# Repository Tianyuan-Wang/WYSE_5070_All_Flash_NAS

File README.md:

# WYSE_5070_All_Flash_NAS

最近买了个二手的WYSE 5070瘦客户机打算用作低功耗NAS。由于不是Extended版本，需要对硬件进行改动来安装额外的硬盘。

之前看了[KCORES的教程](https://youtu.be/9opQ4gsh4Hg?si=m19QCSclOVte6yVY)，给主板加了PCIE插槽但是配套的Riser卡放不进机箱，而且需要搭配12V电源。

于是一切为了美观，设计了一个自带19V转12V的矮版转接卡，配合PCIE桥接卡可以拓展4个M.2 NVME SSD。配合机箱内部预留的螺丝孔位，正好可以3D打印个支架用来固定扩展卡。

## 硬件改动

1. 需要切掉原本用来固定背板扩展卡的两个金属片。以及将3D打印的NVME扩展卡支架用M3x10螺丝安装到机箱内。

2. 需要将NVME扩展卡末端切掉5mm，否则机箱盖子盖不上。（这里用的是SSU SU-EM5204(A3)版的扩展卡，链接就不放了，某宝有卖。）没用更高速的版本是因为散热器高度的问题，这里我把原本10mm的散热片剪成了6mm高度，正好能放下。如果能找到合适的散热片，推荐买高速版本，因为5204-A3上行是3.0x2而主板是2.0x4，浪费了很多。机箱外壳是金属的，可以加散热贴通过机箱散热。

## 安装注意

1. 安装扩展卡的时候，要先把NVME扩展卡插入Riser卡里再一起插入主板PCIE插槽，否则没法装扩展卡。

2. 如果是和我一样用的无EMMC版本的，需要先安装扩展卡支架再安装主板上的SATA SSD。

## 示意图

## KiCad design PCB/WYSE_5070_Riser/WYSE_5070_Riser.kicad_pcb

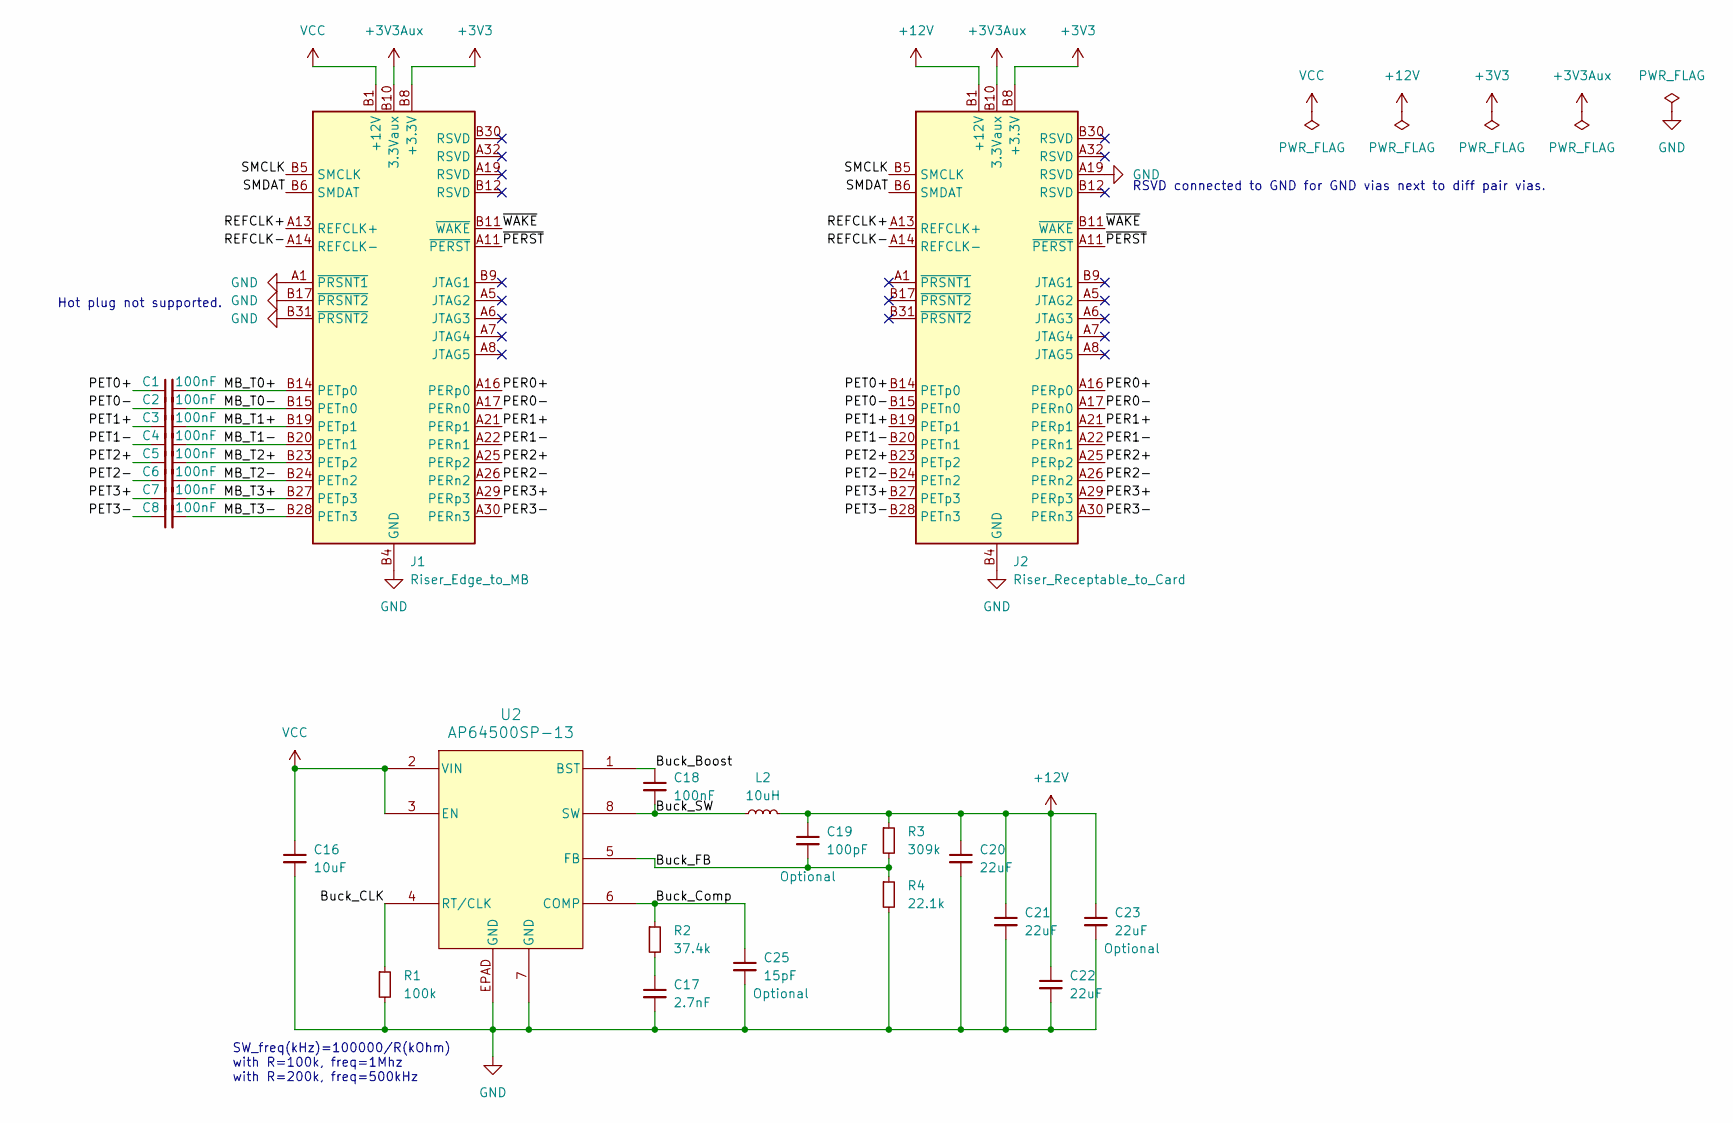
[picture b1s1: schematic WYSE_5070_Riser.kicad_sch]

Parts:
C1, C2, C3, C4, C5, C6, C7, C8, C18: 100nF; C_0402_1005Metric
C16: 10uF; C_1206_3216Metric
C17: 2.7nF; C_0402_1005Metric
C19: 100pF; C_0402_1005Metric
C20, C21, C22, C23: 22uF; C_0805_2012Metric
C25: 15pF; C_0402_1005Metric
J1: Riser_Edge_to_MB; BUS_PCIexpress_x4_Short
J2: Riser_Receptable_to_Card; PCIEx4_SMD_Narrow
L2: 10uH; L_Bourns_SRP1038C_10.0x10.0mm
R1: 100k; R_0402_1005Metric
R2: 37.4k; R_0402_1005Metric
R3: 309k; R_0402_1005Metric
R4: 22.1k; R_0402_1005Metric
U2: AP64500SP-13; SO-8EP_DIO

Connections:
+3V3: J1.A9 (+3.3V), J1.A10 (+3.3V), J1.B8 (+3.3V), J2.A9 (+3.3V), J2.A10 (+3.3V), J2.B8 (+3.3V)
+3V3Aux: J1.B10 (3.3Vaux), J2.B10 (3.3Vaux)
+12V: C19.1, C20.1, C21.1, C22.1, C23.1, J2.A2 (+12V), J2.A3 (+12V), J2.B1 (+12V), J2.B2 (+12V), J2.B3 (+12V), L2.2, R3.1
/Buck_Boost: C18.1, U2.1 (BST)
/Buck_CLK: R1.1, U2.4 (RT/CLK)
/Buck_Comp: C25.1, R2.1, U2.6 (COMP)
/Buck_FB: C19.2, R3.2, R4.1, U2.5 (FB)
/Buck_SW: C18.2, L2.1, U2.8 (SW)
/MB_T0+: C1.2, J1.B14 (PETp0)
/MB_T0-: C2.2, J1.B15 (PETn0)
/MB_T1+: C3.2, J1.B19 (PETp1)
/MB_T1-: C4.2, J1.B20 (PETn1)
/MB_T2+: C5.2, J1.B23 (PETp2)
/MB_T2-: C6.2, J1.B24 (PETn2)
/MB_T3+: C7.2, J1.B27 (PETp3)
/MB_T3-: C8.2, J1.B28 (PETn3)
/PER0+: J1.A16 (PERp0), J2.A16 (PERp0)
/PER0-: J1.A17 (PERn0), J2.A17 (PERn0)
/PER1+: J1.A21 (PERp1), J2.A21 (PERp1)
/PER1-: J1.A22 (PERn1), J2.A22 (PERn1)
/PER2+: J1.A25 (PERp2), J2.A25 (PERp2)
/PER2-: J1.A26 (PERn2), J2.A26 (PERn2)
/PER3+: J1.A29 (PERp3), J2.A29 (PERp3)
/PER3-: J1.A30 (PERn3), J2.A30 (PERn3)
/PET0+: C1.1, J2.B14 (PETp0)
/PET0-: C2.1, J2.B15 (PETn0)
/PET1+: C3.1, J2.B19 (PETp1)
/PET1-: C4.1, J2.B20 (PETn1)
/PET2+: C5.1, J2.B23 (PETp2)
/PET2-: C6.1, J2.B24 (PETn2)
/PET3+: C7.1, J2.B27 (PETp3)
/PET3-: C8.1, J2.B28 (PETn3)
/REFCLK+: J1.A13 (REFCLK+), J2.A13 (REFCLK+)
/REFCLK-: J1.A14 (REFCLK-), J2.A14 (REFCLK-)
/SMCLK: J1.B5 (SMCLK), J2.B5 (SMCLK)
/SMDAT: J1.B6 (SMDAT), J2.B6 (SMDAT)
/~PERST: J1.A11 (~PERST), J2.A11 (~PERST)
/~WAKE: J1.B11 (~WAKE), J2.B11 (~WAKE)
GND: C16.2, C17.2, C20.2, C21.2, C22.2, C23.2, C25.2, J1.A1 (~PRSNT1), J1.A4 (GND), J1.A12 (GND), J1.A15 (GND), J1.A18 (GND), J1.A20 (GND), J1.A23 (GND), J1.A24 (GND), J1.A27 (GND), J1.A28 (GND), J1.A31 (GND), J1.B4 (GND), J1.B7 (GND), J1.B13 (GND), J1.B16 (GND), J1.B17 (~PRSNT2), J1.B18 (GND), J1.B21 (GND), J1.B22 (GND), J1.B25 (GND), J1.B26 (GND), J1.B29 (GND), J1.B31 (~PRSNT2), J1.B32 (GND), J2.A4 (GND), J2.A12 (GND), J2.A15 (GND), J2.A18 (GND), J2.A19 (RSVD), J2.A20 (GND), J2.A23 (GND), J2.A24 (GND), J2.A27 (GND), J2.A28 (GND), J2.A31 (GND), J2.B4 (GND), J2.B7 (GND), J2.B13 (GND), J2.B16 (GND), J2.B18 (GND), J2.B21 (GND), J2.B22 (GND), J2.B25 (GND), J2.B26 (GND), J2.B29 (GND), J2.B32 (GND), R1.2, R4.2, U2.7 (GND), U2.EPAD (GND)
unnamed: C17.1, R2.2
VCC: C16.1, J1.A2 (+12V), J1.A3 (+12V), J1.B1 (+12V), J1.B2 (+12V), J1.B3 (+12V), U2.2 (VIN), U2.3 (EN)

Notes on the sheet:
Hot plug not supported.
SW_freq(kHz)=100000/R(kOhm) with R=100k, freq=1Mhz with R=200k, freq=500kHz
RSVD connected to GND for GND vias next to diff pair vias.

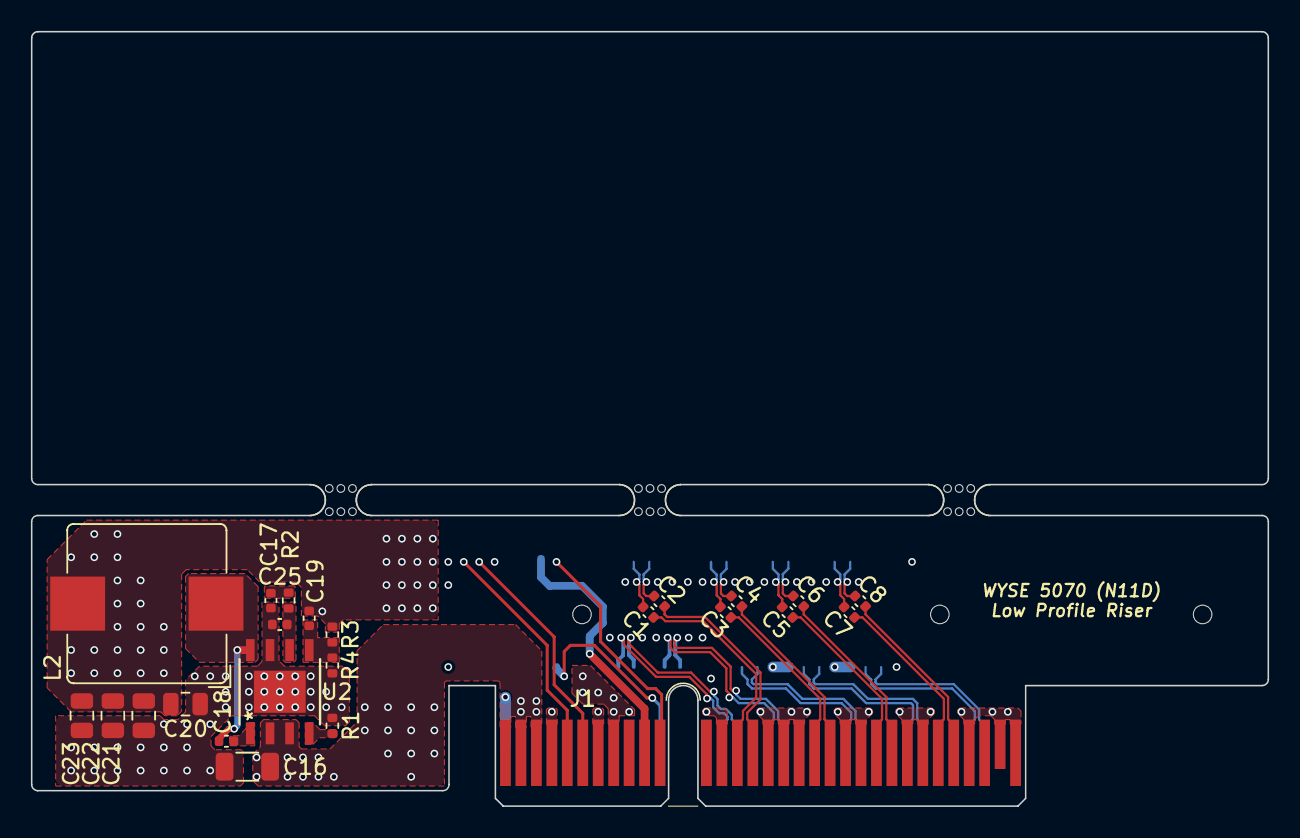
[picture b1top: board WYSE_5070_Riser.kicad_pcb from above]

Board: 4 copper layers, 80.0 x 50.1 mm, 28 parts (1 on the bottom side), 41 nets.

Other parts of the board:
mouse-bite-2mm-slot, mouse-bite-2mm-slot#2, mouse-bite-2mm-slot#3: VAL**; mouse-bite-2mm-slot

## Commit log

2024-02-13 Added all source files.
